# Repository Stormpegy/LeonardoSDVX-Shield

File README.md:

# LeonardoSDVX-Shield

Open source IO shield for homebuilt SDVX / K-Shoot Mania style controllers.

Uses the kicad libraries by sparkfun 
https://github.com/sparkfun/SparkFun-KiCad-Libraries

Uses arduino-kicad-library by Alarm-Siren
https://github.com/Alarm-Siren/arduino-kicad-library

Originally built to use the cons&stuff leovxhq code but pinout has been modified to make some of the routing neater.

Cons&Stuff SDVX guide
[Cons&Stuff](https://consandstuff.github.io/rhythmcons/sound-voltex/sdvx-normal/)

Original code can be found here
[Cons & Stuff leovx Code](https://github.com/consandstuff/sdvx-diy/tree/master/code%20Leonardo/Arduino%20Leonardo)

LED Pinout code changes between original leovx/leovxhq and what is required for this board.  
To update this code look for line 18 on leovx or line 27 on leovxhq and replace with the new example.

Original
`uint8_t ledPins[] = {6,7,8,9,10,11,12};`

New
`uint8_t ledPins[] = {12,11,10,9,8,7,6};`

I won't tell you how to open and flash this code, just download the arduino IDE and google the rest, It's not too complicated, ask on discord if you need a hand.

## Changelog
REV 2 released

- Replaced JST-XH connector footprints with generic 2.54mm header footprints, original footprints were well out of spec and didn't fit 2.54mm headers/plugs; thank you SirusDoma (C&S discord) for bringing this to my attention.

- System pin rotated to have GND on the same side as all other connections (I have also forgotten why the system pin exists but I'm leaving it there /shrug)

- Removed white border on leonardo shield footprint, library updated and included.

## Pinout

|Button	| Pin # | Button # | LED Pin # |
|-------|-------|----------|-----------|
|Start	| 13 | Button 1 | 12 |
|BT-A	| A0 | Button 2 | 11 |
|FX-L	| A1 | Button 3 | 10 |
|BT-B	| A2 | Button 4 | 9 |
|BT-C	| A3 | Button 5 | 8 |
|FX-R	| A4 | Button 6 | 7 |
|BT-D	| A5 | Button 7 | 6 |

Encoders | DATA 1 | DATA 2 |
|--------|--------|--------|
|Left knob  (VOL-L) | 0 | 1 |
|Right knob (VOL-R) | 2 | 3 |

## Images

## Parts and construction

x32 header pins, standard 2.54mm spacing (Optional +2 if you wish to put headers on the system pins)

Very cheap, Can be found for as cheap as $1USD for 10pcs 40pin online.

x9 JST-XH 4 Pin style straight THT connectors (Ensure you get straight through hole, you will ~~likely~~ definitely struggle if you get right angle or smd)

These XH connectors can be found as sets with cables as well, It's recommend to get 25-35cm wires if you get a set.
JST brand is not important, Just ensure they are XH style spacing (2.5mm/2.54mm)

Crimps, Buttons, Leonardo and all the other parts to build a controller are also required but this just covers the parts for this shield, reference the cons&stuff for a great guide on making your own controller.

## Ordering
These can be ordered very cheaply through a PCB manufacturer such as JLCPCB, they cost $2USD for 5-10qty and shipping is around $5USD to Malaysia and $6USD to Australia.

Simply download LeonardoSDVX-Shield-Gerber.zip and upload it to your preferred PCB manufacturer, I use JLCPCB though there are plenty out there.

I highly recommend leaving the settings on JLCPCB as default unless you know what you're doing.

Layers - 2

Dimensions - 53 x 69 mm, don't change, it automatically enters these.

PCB thickness - 1.6mm

PCB Colour - Feel free to change this one though it will cost more, they use black silkscreen for white pcbs and white silkscreen for everything else.

Surface - HASL (with lead) (Other options are more expensive and not worth it for this simple board)

Copper weight - 1oz

Gold fingers - No

Panel - No

Different design - 1

## To do list
- [x] Make parts list

- [x] Add imgs to readme.md (this doc)

- [x] Add more info on the code change / LED pinout change

- [x] Modify the shield footprint to remove the white outline? unsure how that will go with manufacturing

- [x] Fix the big mistake on rev 1 :)

## Contact and Modifications
Created by https://github.com/Stormpegy
Feel free to contact me in the cons&stuff discord server under the same username for any assistance.

Cons&stuff discord can be found here.  
https://consandstuff.github.io/

Feel free to modify and redistribute this design in any way you please just give credit for original design and keep appropriate links and licenses for the used libraries.

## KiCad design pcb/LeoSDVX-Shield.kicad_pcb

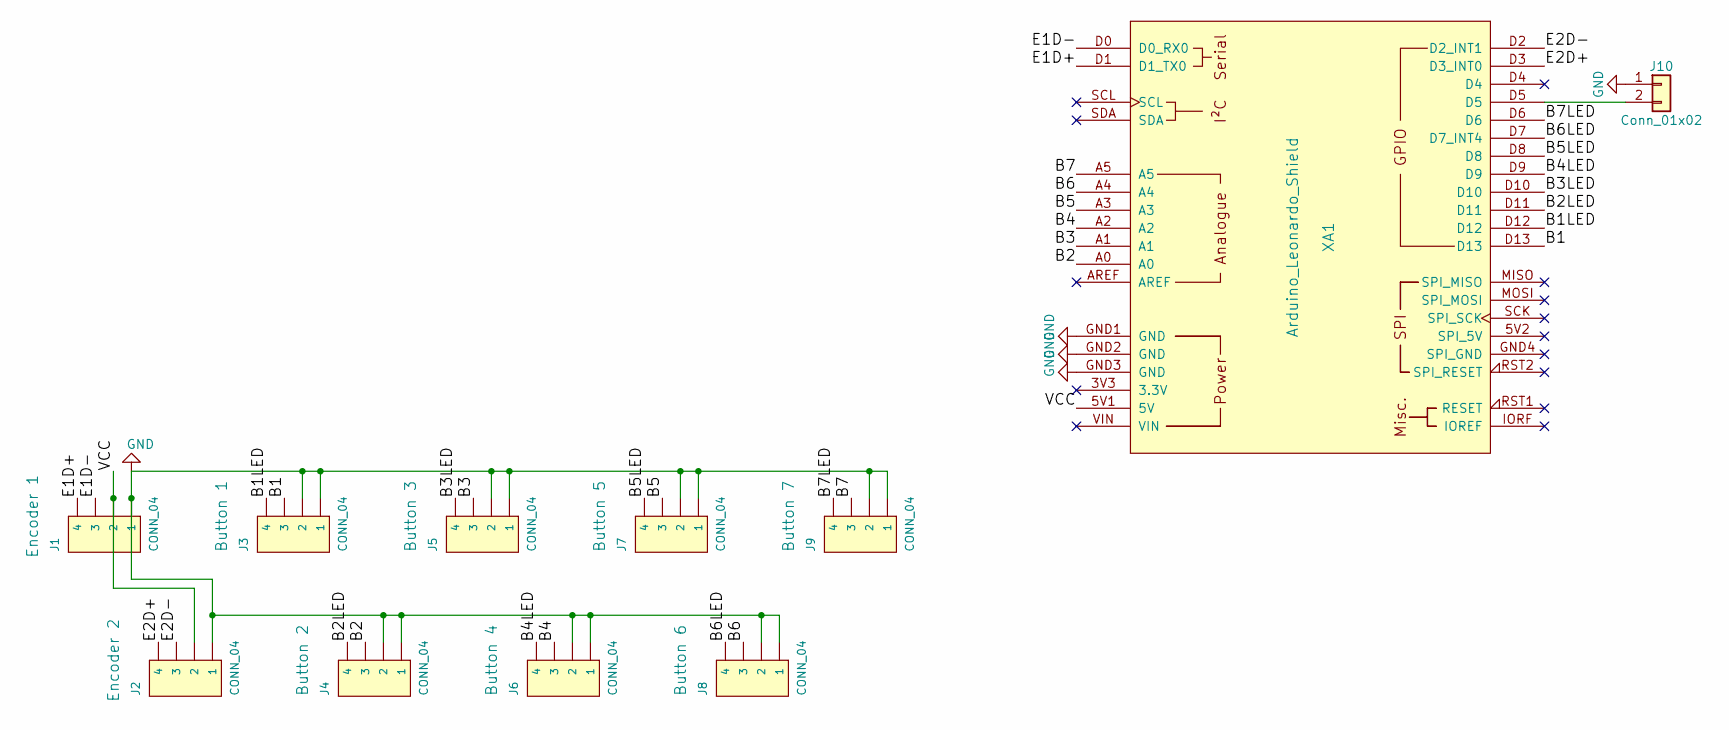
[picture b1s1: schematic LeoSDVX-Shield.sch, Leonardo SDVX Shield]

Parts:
J1, J2, J3, J4, J5, J6, J7, J8, J9: CONN_04; Pin_Header_Straight_1x04_Pitch2.54mm
J10: Conn_01x02; Pin_Header_Straight_1x02_Pitch2.54mm
XA1: Arduino_Leonardo_Shield; Arduino_Leonardo_Shield_noborder

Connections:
/B1: J3.3, XA1.D13
/B1LED: J3.4, XA1.D12
/B2: J4.3, XA1.A0
/B2LED: J4.4, XA1.D11
/B3: J5.3, XA1.A1
/B3LED: J5.4, XA1.D10
/B4: J6.3, XA1.A2
/B4LED: J6.4, XA1.D9
/B5: J7.3, XA1.A3
/B5LED: J7.4, XA1.D8
/B6: J8.3, XA1.A4
/B6LED: J8.4, XA1.D7 (D7_INT4)
/B7: J9.3, XA1.A5
/B7LED: J9.4, XA1.D6
/E1D+: J1.4, XA1.D1 (D1_TX0)
/E1D-: J1.3, XA1.D0 (D0_RX0)
/E2D+: J2.4, XA1.D3 (D3_INT0)
/E2D-: J2.3, XA1.D2 (D2_INT1)
/VCC: J1.2, J2.2, XA1.5V1 (5V)
GND: J1.1, J2.1, J3.1, J3.2, J4.1, J4.2, J5.1, J5.2, J6.1, J6.2, J7.1, J7.2, J8.1, J8.2, J9.1, J9.2, J10.1, XA1.GND1 (GND), XA1.GND2 (GND), XA1.GND3 (GND)
unnamed: J10.2, XA1.D5

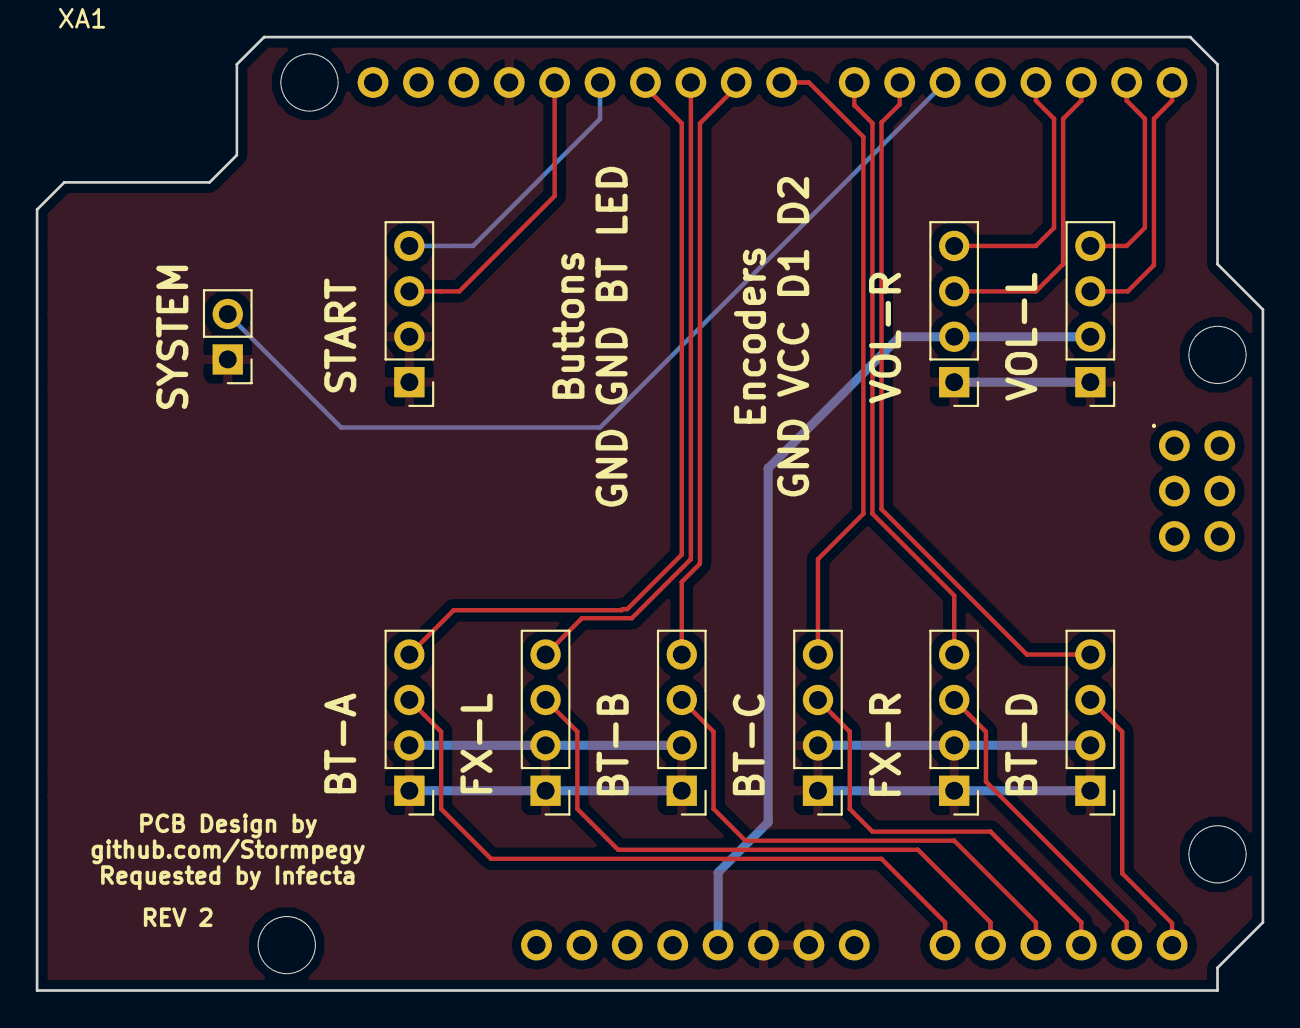
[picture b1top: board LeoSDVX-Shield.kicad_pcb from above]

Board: 2 copper layers, 68.6 x 53.3 mm, 11 parts (0 on the bottom side), 21 nets.

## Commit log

2018-08-10 Gerber added, Imgs added
    Created v1 gerber files
    Added images of the pcb
    Updated readme, added to do list
2018-08-10 Update to readme.md
    I should really edit this in browser so I can preview it.....
2018-08-10 Update to readme.md
    Added Images
2018-08-10 Update to various
    Updated readme.md
    -Updated ordering section
    -Added item to to do list
    Updated pcb design
    -Moved 1 trace to match others and updated gnd fill
    Updated gerbers to match the pcb update
2018-08-10 Update to readme.md
    Updated readme.md
    -Added Parts and Construction header
    --Contains information on the other components needed
    -Ticked off "make parts list" on the to do list
2018-08-11 Update to readme.md
    Updated readme.md
    -Fixed some spelling/formatting
    -Added a little more info onc changing the code
    -Ticked off "add more info on the code" on the to do list
    Might still add some more info on that though, I think it's explained enough for now.
2019-05-06 Revision 2
    REV 2 released
    - Replaced JST-XH connector footprints with generic 2.54mm header footprints, original footprints were well out of spec and didn't fit 2.54mm headers/plugs; thank you SirusDoma (C&S discord) for brin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
    - System pin rotated to have GND on the same side as all other connections (I have also forgotten why the system pin exists but I'm leaving it there /shrug)
    - Removed white border on leonardo shield footprint, library updated and included
    Hopefully the last update this will need
2020-04-27 Update README.md
    i fix formatting and put fullstops where they legally should be :)
